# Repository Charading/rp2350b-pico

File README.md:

# RP2350B Pico Board

This is a custom RP2350B development board designed to match the **Raspberry Pi Pico** form factor.  
It keeps a similar form factor but is extended by a few pins, in order to break out all 8 analog gpio.

---

## Features
- **RP2350B microcontroller**
- **Pico-compatible pinout**
- **USB-C connector**
- **WS2812 RGB LED** on **GPIO16**
- **BOOT** and **RESET** buttons
- **Castellated edges** for module or breadboard use

---

## Notes
- The WS2812 LED on **GPIO16** can be controlled using any standard NeoPixel or WS2812 library.
- The board powers from **USB 5V (VBUS)** through a Schottky diode to **VSYS**,  
  then regulated down to **3.3V** for the MCU.
- Fully compatible with the **Raspberry Pi Pico SDK**, **MicroPython**, and **CircuitPython**.

### Expansion Board
I also created a small expansion board since it doesn't follow the exact layout as the original Pico.

---

Designed for experimentation and easy migration from RP2040 to RP2350 as I wanted more analog pins for a project.
Inspiration taken from  [pico-stretch](https://github.com/jvanderberg/pico-stretch) by [jvanderberg](https://github.com/jvanderberg)

---

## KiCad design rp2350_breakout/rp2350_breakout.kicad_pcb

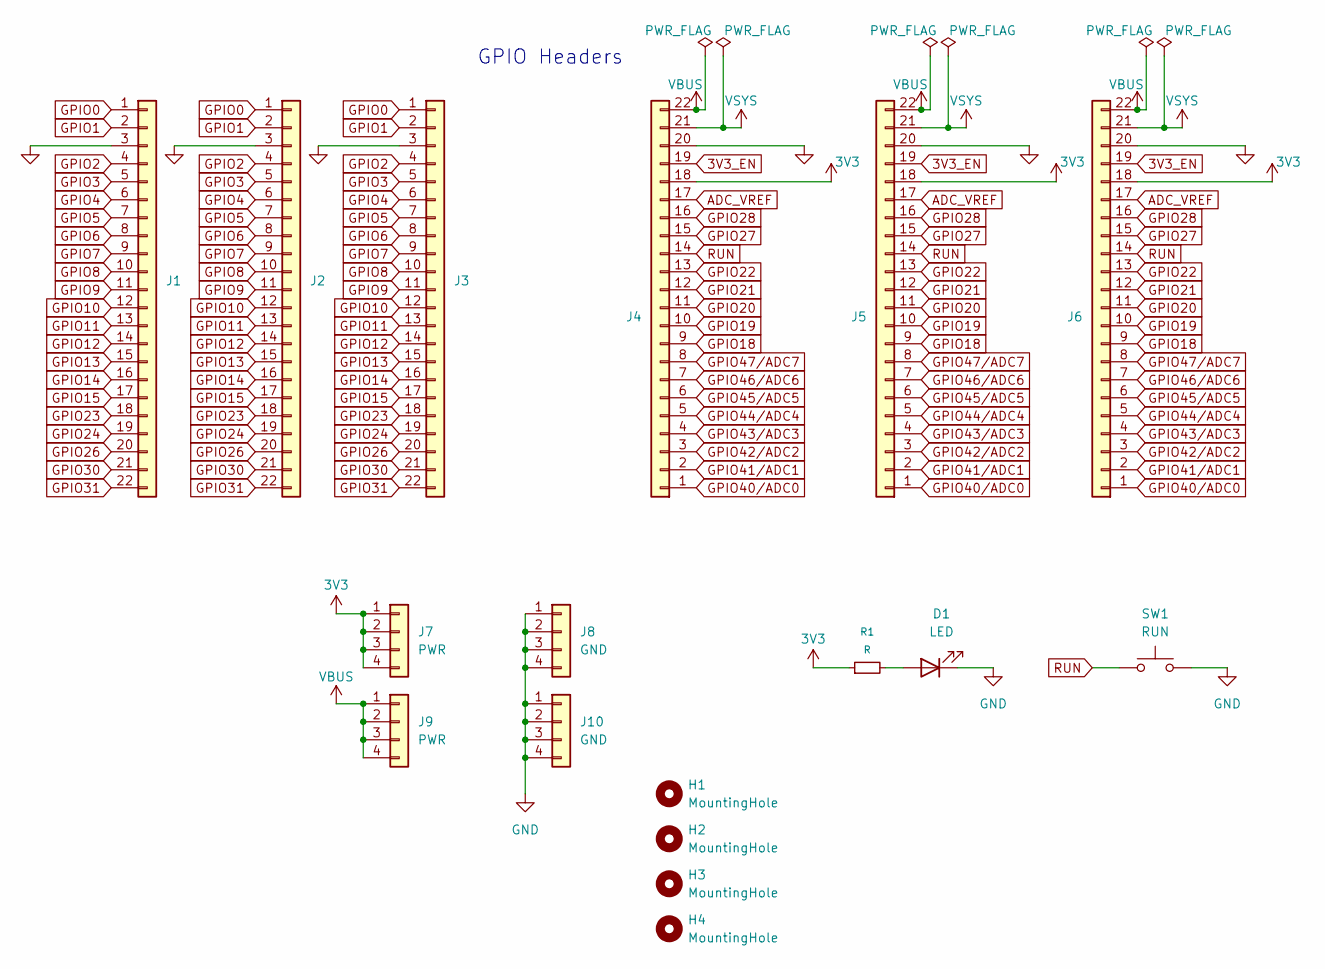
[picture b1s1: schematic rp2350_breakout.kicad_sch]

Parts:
D1: LED; LED_0805_2012Metric
H1, H2, H3, H4: MountingHole; MountingHole_2.2mm_M2
J1, J2, J3, J4, J5, J6: Conn_01x32_MountingPin; Mars_Clean_Connector_01x22_PinHeader_2.54mm
J7, J9: PWR; SWD_Debug_PinHeader_1x04_P2.54mm; Part Number 1-0401FBV0T
J8, J10: GND; SWD_Debug_PinHeader_1x04_P2.54mm; Part Number 1-0401FBV0T
R1: R; R_0805
SW1: RUN; SW_TH_Tactile_Omron_B3F-102x

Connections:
3V3: J4.18, J5.18, J6.18, J7.1, J7.2, J7.3, J7.4, R1.1
3V3_EN: J4.19, J5.19, J6.19
ADC_VREF: J4.17, J5.17, J6.17
GND: D1.1 (K), J1.3, J2.3, J3.3, J4.20, J5.20, J6.20, J8.1, J8.2, J8.3, J8.4, J10.1, J10.2, J10.3, J10.4, SW1.2; also elsewhere on the board
GPIO0: J1.1, J2.1, J3.1
GPIO1: J1.2, J2.2, J3.2
GPIO2: J1.4, J2.4, J3.4
GPIO3: J1.5, J2.5, J3.5
GPIO4: J1.6, J2.6, J3.6
GPIO5: J1.7, J2.7, J3.7
GPIO6: J1.8, J2.8, J3.8
GPIO7: J1.9, J2.9, J3.9
GPIO8: J1.10, J2.10, J3.10
GPIO9: J1.11, J2.11, J3.11
GPIO10: J1.12, J2.12, J3.12
GPIO11: J1.13, J2.13, J3.13
GPIO12: J1.14, J2.14, J3.14
GPIO13: J1.15, J2.15, J3.15
GPIO14: J1.16, J2.16, J3.16
GPIO15: J1.17, J2.17, J3.17
GPIO18: J4.9, J5.9, J6.9
GPIO19: J4.10, J5.10, J6.10
GPIO20: J4.11, J5.11, J6.11
GPIO21: J4.12, J5.12, J6.12
GPIO22: J4.13, J5.13, J6.13
GPIO23: J1.18, J2.18, J3.18
GPIO24: J1.19, J2.19, J3.19
GPIO26: J1.20, J2.20, J3.20
GPIO27: J4.15, J5.15, J6.15
GPIO28: J4.16, J5.16, J6.16
GPIO30: J1.21 (Pin_19), J2.21 (Pin_19), J3.21 (Pin_19)
GPIO31: J1.22 (Pin_20), J2.22 (Pin_20), J3.22 (Pin_20)
GPIO40/ADC0: J4.1, J5.1, J6.1
GPIO41/ADC1: J4.2, J5.2, J6.2
GPIO42/ADC2: J4.3, J5.3, J6.3
GPIO43/ADC3: J4.4, J5.4, J6.4
GPIO44/ADC4: J4.5, J5.5, J6.5
GPIO45/ADC5: J4.6, J5.6, J6.6
GPIO46/ADC6: J4.7, J5.7, J6.7
GPIO47/ADC7: J4.8, J5.8, J6.8
unnamed 40: D1.2 (A), R1.2; also elsewhere on the board
RUN: J4.14, J5.14, J6.14, SW1.1
VBUS: J4.22 (Pin_20), J5.22 (Pin_20), J6.22 (Pin_20), J9.1, J9.2, J9.3, J9.4
VSYS: J4.21 (Pin_19), J5.21 (Pin_19), J6.21 (Pin_19)

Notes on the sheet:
GPIO Headers

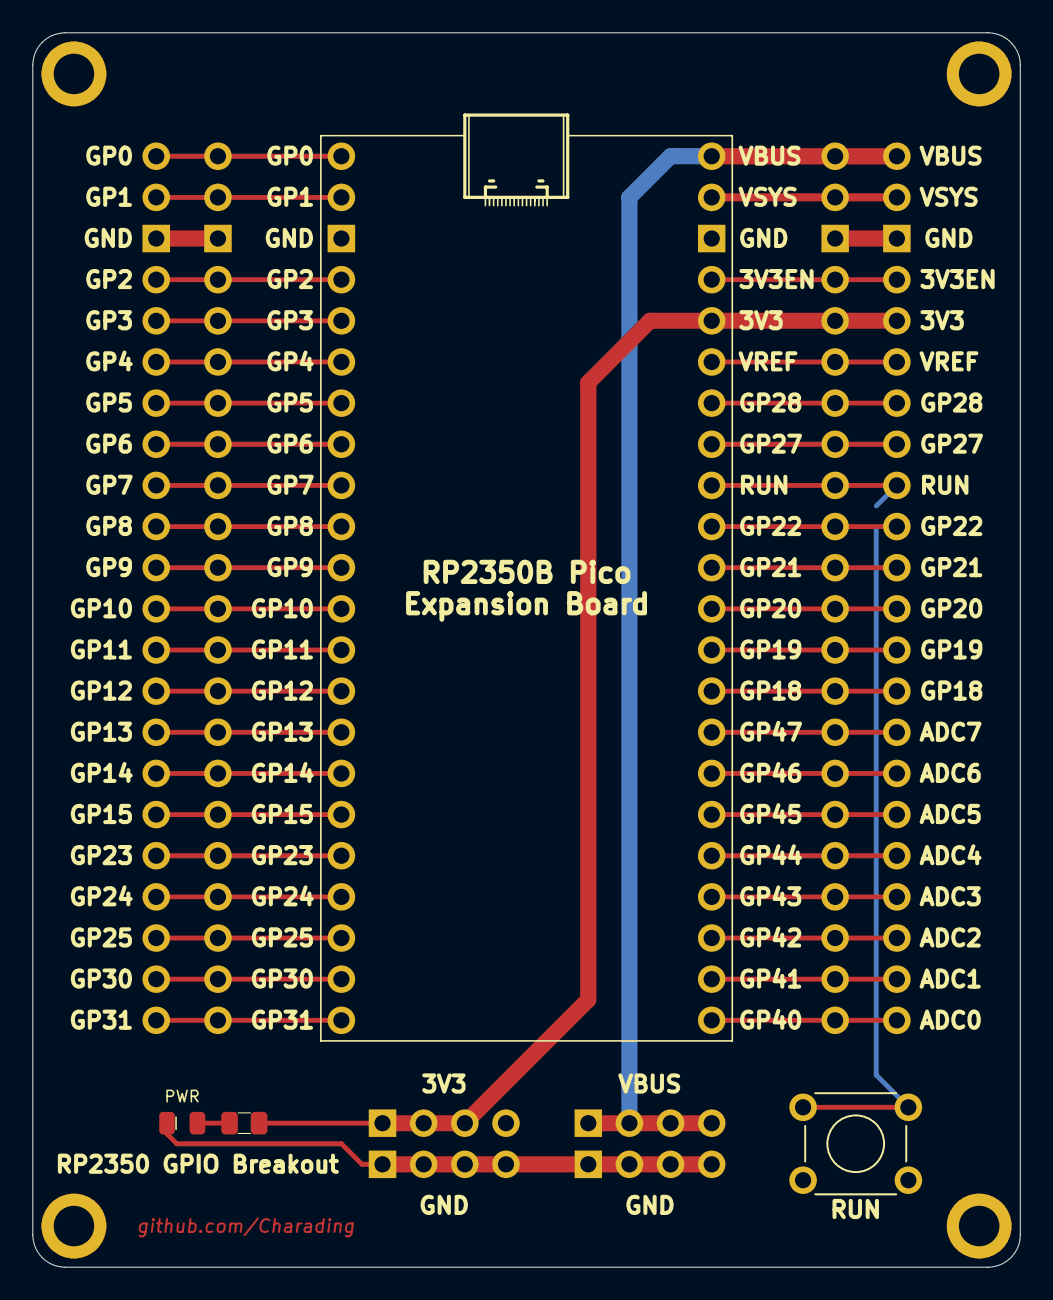
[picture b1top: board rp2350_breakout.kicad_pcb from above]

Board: 2 copper layers, 61.0 x 76.2 mm, 17 parts (0 on the bottom side), 44 nets.

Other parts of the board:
PWR: LED; LED_0805_2012Metric

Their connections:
GND: PWR.1 (K); also elsewhere on the board
unnamed 40: PWR.2 (A); also elsewhere on the board

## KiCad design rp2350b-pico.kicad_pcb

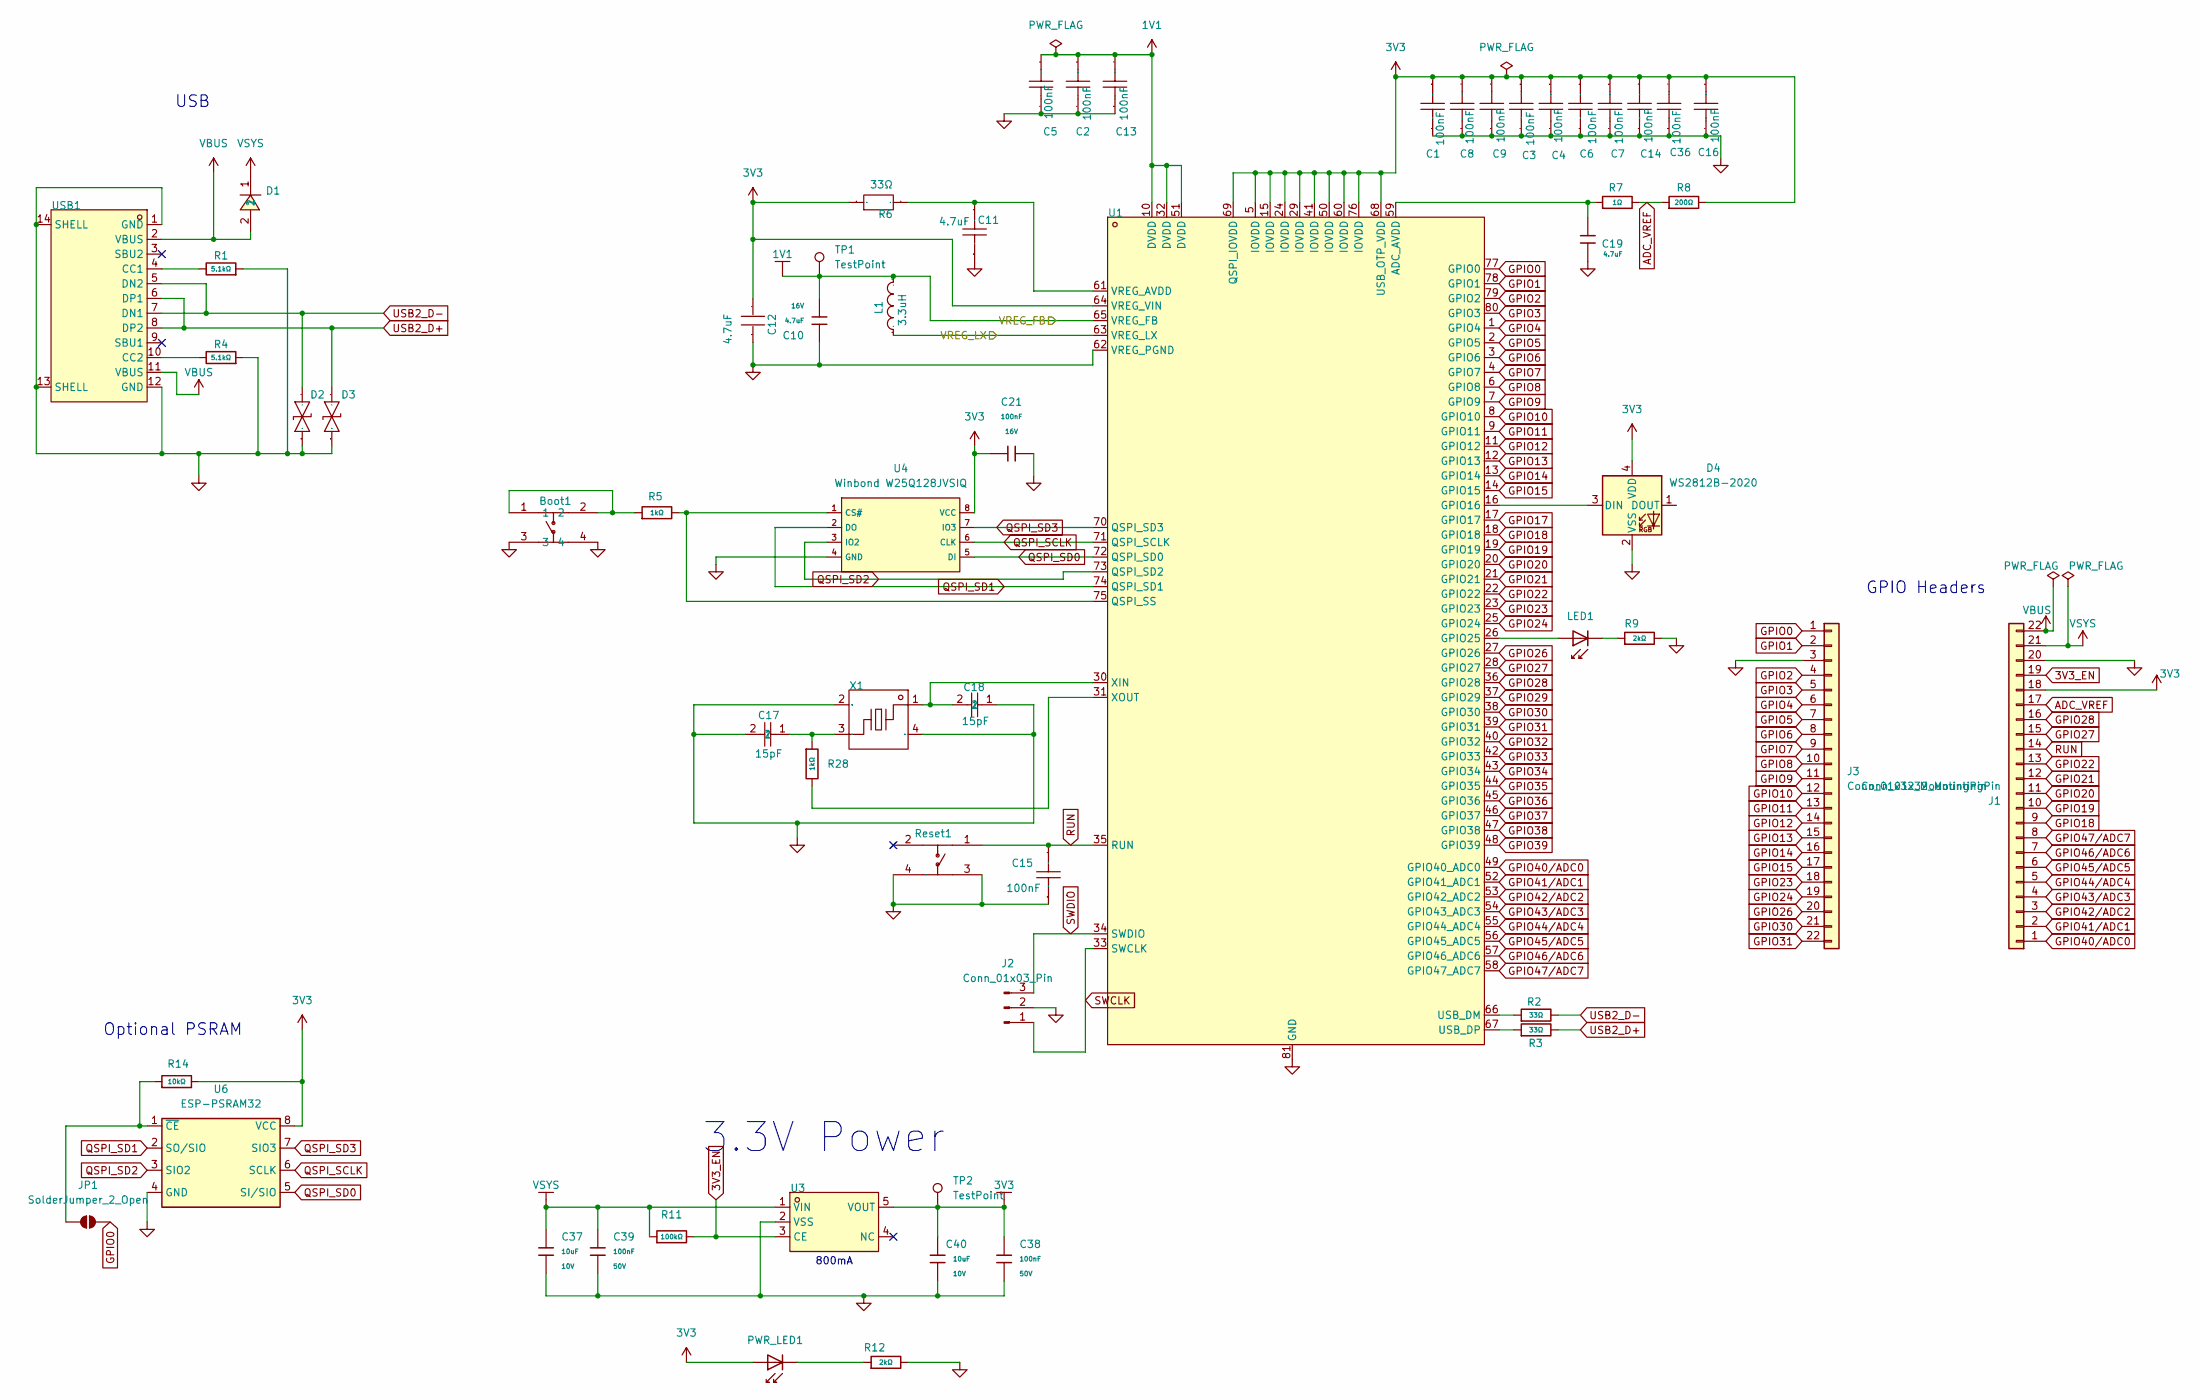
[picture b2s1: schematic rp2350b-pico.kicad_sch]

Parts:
Boot1: K2-1808SN-A4SW-01; KEY-SMD_4P-L4.2-W3.2-P2.20-LS5.1-TL; Manufacturer Part K2-1808SN-A4SW-01; LCSC Part Name 4.2mm*3.25mm
C1, C2, C3, C4, C5, C6, C7, C8, C13, C14, C16, C36: 100nF; C0402; Manufacturer Part CL05B104KO5NNNC; LCSC Part Name 100nF ±10% 16V
C9, C15: 100nF; C0402; Voltage Rating 50V; Manufacturer Part CC0603KRX7R9BB104; LCSC Part Name 100nF ±10% 50V
C10: 4.7uF; C_0603; Voltage Rated 16V; Tolerance ±10%; Part CL10A475KO8NNNC; LCSC C19666
C11: 4.7uF; Manufacturer Part CL05A475MP5NRNC; LCSC Part Name 4.7uF ±20% 10V
C12: 4.7uF; Manufacturer Part CL10A475KO8NNNC; LCSC Part Name 4.7uF ±10% 16V
C17, C18: 15pF; C0402; Manufacturer Part 0402CG150J500NT; LCSC Part Name 15pF ±5% 50V
C19: 4.7uF; C_0402; Voltage Rated 10V; Tolerance ±20%; Part CL05A475MP5NRNC; LCSC C23733
C21: 100nF; C_0402; Voltage Rated 16V; Tolerance ±10%; Part CL05B104KO5NNNC; LCSC C1525
C37, C40: 10uF; C_0603; Voltage Rated 10V; Tolerance ±10%; Part CL10A106KP8NNNC; LCSC C19702
C38, C39: 100nF; C_0603; Voltage Rated 50V; Tolerance ±10%; Part CC0603KRX7R9BB104; LCSC C14663
D1: POWERDI-123_L2.8-W1.8-LS3.7-RD; Manufacturer Part DFLS130L-7; LCSC Part Name 电压:30V 电流:1A
D2, D3: RCLAMP0521P.TCT-MS; D0402-BI; Manufacturer Part RCLAMP0521P.TCT-MS; LCSC Part Name 双向TVS 5V截止 4A峰值脉冲 丝印N
D4: WS2812B-2020; LED_WS2812B-2020_PLCC4_2.0x2.0mm
J1, J3: Conn_01x32_MountingPin; Pico_22pin
J2: Conn_01x03_Pin; PinHeader_1x03_P2.54mm_Vertical
JP1: SolderJumper_2_Open; JUMPER_SMD_1x2_tiny
L1: IND-SMD_L2.0-W1.6_AOTA-B201610S3R3-101-T; Manufacturer Part AOTA-B201610S3R3-101-T; LCSC Part Name AOTA-B201610S3R3-101-T
LED1: Red; Mars_LED_0603; Part KT-0603R; LCSC C2286
PWR_LED1: Red; D_0603; Part KT-0603R; LCSC C2286
R1, R4: 5.1kΩ; R_0402; Overload Voltage (Max) 50V; Tolerance ±1%; Part 0402WGF5101TCE; LCSC C25905
R2, R3: 33Ω; R_0402; Overload Voltage (Max) 50V; Tolerance ±1%; Part 0402WGF330JTCE; LCSC C25105
R5: 1kΩ; R_0402; Overload Voltage (Max) 50V; Tolerance ±1%; Part 0402WGF1001TCE; LCSC C11702
R6: 33Ω; R0402; Manufacturer Part 0402WGF330JTCE; LCSC Part Name 33Ω ±1% 62.5mW 厚膜电阻
R7: 1Ω; R_0603; Overload Voltage (Max) 75V; Tolerance ±1%; Part 0603WAF100KT5E; LCSC C22936
R8: 200Ω; R_0603; Overload Voltage (Max) 75V; Tolerance ±1%; Part 0603WAF2000T5E; LCSC C8218
R9, R12: 2kΩ; R_0402; Overload Voltage (Max) 50V; Tolerance ±1%; Part 0402WGF2001TCE; LCSC C4109
R11: 100kΩ; R_0402; Overload Voltage (Max) 50V; Tolerance ±1%; Part 0402WGF1003TCE; LCSC C25741
R14: 10kΩ; R_0402; Overload Voltage (Max) 50V; Tolerance ±1%; Part 0402WGF1002TCE; LCSC C25744
R28: 1kΩ; R_0603; Overload Voltage (Max) 75V; Tolerance ±1%; Part 0603WAF1001T5E; LCSC C21190
Reset1: K2-1808SN-A4SW-01; KEY-SMD_4P-L4.2-W3.2-P2.20-LS5.1-TL; Manufacturer Part K2-1808SN-A4SW-01; LCSC Part Name 4.2mm*3.25mm
TP1, TP2: TestPoint; TestPoint_Pad_1.0x1.0mm
U1: QFN-80_L10.0-W10.0-P0.40-TL-EP3.4; Manufacturer Part RP2350B; LCSC Part Name RP2350B
U3: SOT-23-5_L3.0-W1.7-P0.95-LS2.8-BR; Manufacturer Part ME6217C33M5G; LCSC Part Name ME6217C33M5G
U4: Winbond W25Q128JVSIQ; SOIC-8_L5.3-W5.3-P1.27-LS8.0-BL; Part W25Q128JVSIQ; LCSC C97521
U6: ESP-PSRAM32; SOIC-8_3.9x4.9mm_P1.27mm
USB1: USB-C-SMD_TYPE-C-6PIN-2MD-073; Manufacturer Part TYPE-C 16PIN 2MD(073); LCSC Part Name Type-C 母 卧贴
X1: Manufacturer Part ABM8-272-T3; LCSC Part Name ABM8-272-T3

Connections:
1V1: C2.1, C5.1, C10.2, C13.2, L1.2, TP1.1, U1.10 (DVDD), U1.32 (DVDD), U1.51 (DVDD), U1.65 (VREG_FB)
3V3: C1.1, C3.1, C4.1, C6.1, C7.1, C8.2, C9.2, C12.2, C14.2, C16.1, C21.1, C36.2, C38.1, C40.1, D4.4 (VDD), J1.18, PWR_LED1.2, R6.1, R8.2, R14.2, TP2.1, U1.5 (IOVDD), U1.15 (IOVDD), U1.24 (IOVDD), U1.29 (IOVDD), U1.41 (IOVDD), U1.50 (IOVDD), U1.60 (IOVDD), U1.64 (VREG_VIN), U1.68 (USB_OTP_VDD), U1.69 (QSPI_IOVDD), U1.76 (IOVDD), U3.5 (VOUT), U4.8 (VCC), U6.8 (VCC); also elsewhere on the board
3V3_EN: J1.19, R11.2, U3.3 (CE)
/VREG_LX: L1.1, U1.63 (VREG_LX)
ADC_VREF: J1.17, R7.2, R8.1
GND: Boot1.3, Boot1.4, C1.2, C2.2, C3.2, C4.2, C5.2, C6.2, C7.2, C8.1, C9.1, C10.1, C11.1, C12.1, C13.1, C14.1, C15.1, C16.2, C17.2, C18.1, C19.2, C21.2, C36.1, C37.2, C38.2, C39.2, C40.2, D2.1, D3.1, D4.2 (VSS), J1.20, J2.2, J3.3, R1.1, R4.1, R9.2, R12.2, Reset1.3, Reset1.4, U1.62 (VREG_PGND), U1.81 (GND), U3.2 (VSS), U4.4 (GND), U6.4 (GND), USB1.1 (GND), USB1.12 (GND), USB1.13 (SHELL), USB1.14 (SHELL), X1.2 (GND), X1.4 (GND); also elsewhere on the board
GPIO0: J3.1, JP1.2 (B), U1.77 (GPIO0)
GPIO1: J3.2, U1.78 (GPIO1)
GPIO2: J3.4, U1.79 (GPIO2)
GPIO3: J3.5, U1.80 (GPIO3)
GPIO4: J3.6, U1.1 (GPIO4)
GPIO5: J3.7, U1.2 (GPIO5)
GPIO6: J3.8, U1.3 (GPIO6)
GPIO7: J3.9, U1.4 (GPIO7)
GPIO8: J3.10, U1.6 (GPIO8)
GPIO9: J3.11, U1.7 (GPIO9)
GPIO10: J3.12, U1.8 (GPIO10)
GPIO11: J3.13, U1.9 (GPIO11)
GPIO12: J3.14, U1.11 (GPIO12)
GPIO13: J3.15, U1.12 (GPIO13)
GPIO14: J3.16, U1.13 (GPIO14)
GPIO15: J3.17, U1.14 (GPIO15)
GPIO17: U1.17 (GPIO17)
GPIO18: J1.9, U1.18 (GPIO18)
GPIO19: J1.10, U1.19 (GPIO19)
GPIO20: J1.11, U1.20 (GPIO20)
GPIO21: J1.12, U1.21 (GPIO21)
GPIO22: J1.13, U1.22 (GPIO22)
GPIO23: J3.18, U1.23 (GPIO23)
GPIO24: J3.19, U1.25 (GPIO24)
GPIO26: J3.20, U1.27 (GPIO26)
GPIO27: J1.15, U1.28 (GPIO27)
GPIO28: J1.16, U1.36 (GPIO28)
GPIO29: U1.37 (GPIO29)
GPIO30: J3.21 (Pin_19), U1.38 (GPIO30)
GPIO31: J3.22 (Pin_20), U1.39 (GPIO31)
GPIO32: U1.40 (GPIO32)
GPIO33: U1.42 (GPIO33)
GPIO34: U1.43 (GPIO34)
GPIO35: U1.44 (GPIO35)
GPIO36: U1.45 (GPIO36)
GPIO37: U1.46 (GPIO37)
GPIO38: U1.47 (GPIO38)
GPIO39: U1.48 (GPIO39)
GPIO40/ADC0: J1.1, U1.49 (GPIO40_ADC0)
GPIO41/ADC1: J1.2, U1.52 (GPIO41_ADC1)
GPIO42/ADC2: J1.3, U1.53 (GPIO42_ADC2)
GPIO43/ADC3: J1.4, U1.54 (GPIO43_ADC3)
GPIO44/ADC4: J1.5, U1.55 (GPIO44_ADC4)
GPIO45/ADC5: J1.6, U1.56 (GPIO45_ADC5)
GPIO46/ADC6: J1.7, U1.57 (GPIO46_ADC6)
GPIO47/ADC7: J1.8, U1.58 (GPIO47_ADC7)
unnamed: Boot1.1, Boot1.2, R5.1
unnamed: C17.1, R28.1, X1.3
unnamed: D4.3 (DIN), U1.16 (GPIO16)
unnamed: JP1.1 (A), R14.1, U6.1 (~CE)
unnamed: LED1.1, R9.1
unnamed: PWR_LED1.1, R12.1
unnamed: C19.1, R7.1, U1.59 (ADC_AVDD)
unnamed: LED1.2, U1.26 (GPIO25)
unnamed: R5.2, U1.75 (QSPI_SS), U4.1 (CS#)
unnamed: R2.1, U1.66 (USB_DM)
unnamed: R3.1, U1.67 (USB_DP)
unnamed: C11.2, R6.2, U1.61 (VREG_AVDD)
unnamed: C18.2, U1.30 (XIN), X1.1
unnamed: R28.2, U1.31 (XOUT)
unnamed: R1.2, USB1.4 (CC1)
unnamed: R4.2, USB1.10 (CC2)
QSPI_SCLK: U1.71 (QSPI_SCLK), U4.6 (CLK), U6.6 (SCLK)
QSPI_SD0: U1.72 (QSPI_SD0), U4.5 (DI), U6.5 (SI/SIO)
QSPI_SD1: U1.74 (QSPI_SD1), U4.2 (DO), U6.2 (SO/SIO)
QSPI_SD2: U1.73 (QSPI_SD2), U4.3 (IO2), U6.3 (SIO2)
QSPI_SD3: U1.70 (QSPI_SD3), U4.7 (IO3), U6.7 (SIO3)
RUN: C15.2, J1.14, Reset1.1, U1.35 (RUN)
SWCLK: J2.1, U1.33 (SWCLK)
SWDIO: J2.3, U1.34 (SWDIO)
USB2_D+: D3.2, R3.2, USB1.6 (DP1), USB1.8 (DP2)
USB2_D-: D2.2, R2.2, USB1.5 (DN2), USB1.7 (DN1)
VBUS: D1.2, J1.22 (Pin_20), USB1.2 (VBUS), USB1.11 (VBUS)
VSYS: C37.1, C39.1, D1.1, J1.21 (Pin_19), R11.1, U3.1 (VIN)

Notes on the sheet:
Optional PSRAM
3.3V Power
GPIO Headers
USB
800mA

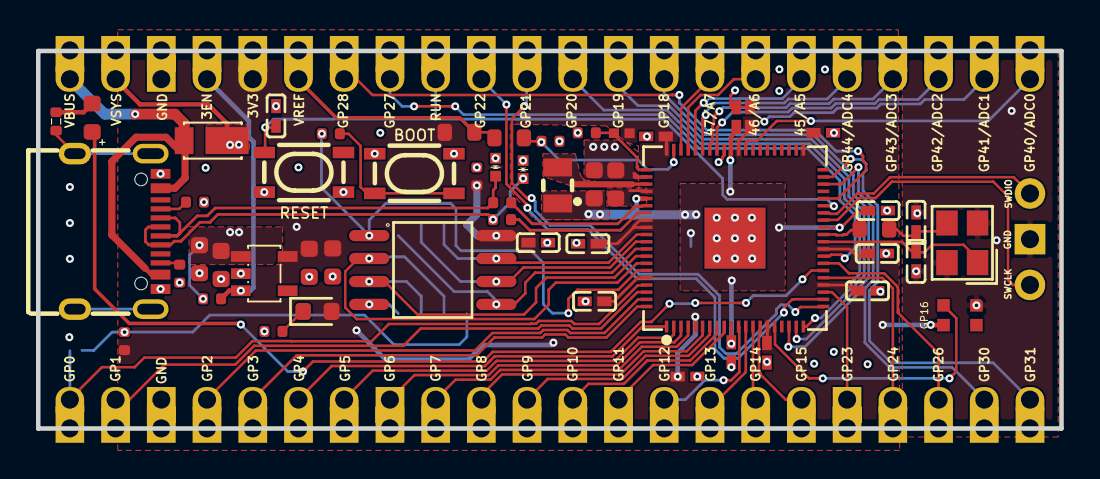
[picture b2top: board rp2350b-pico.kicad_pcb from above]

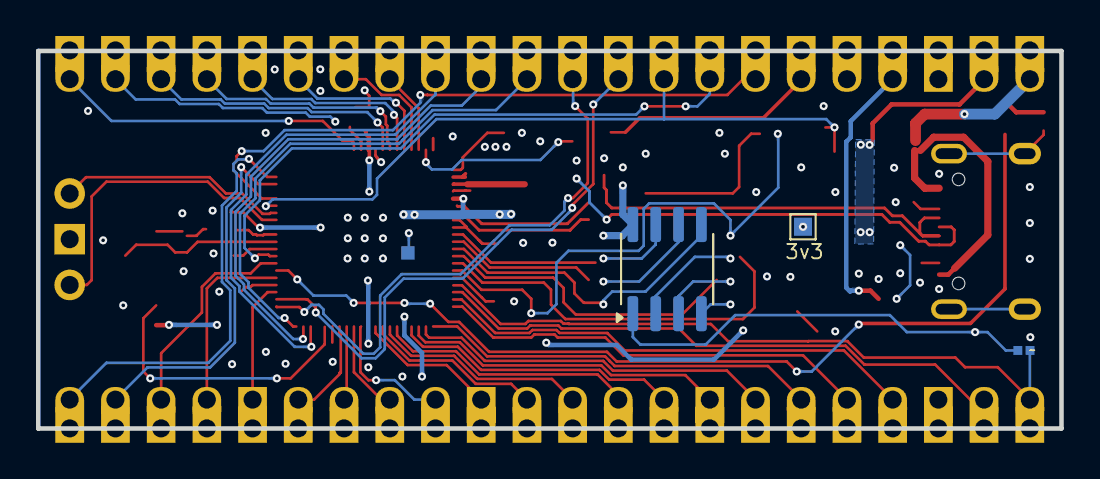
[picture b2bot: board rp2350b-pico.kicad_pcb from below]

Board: 4 copper layers, 56.8 x 21.0 mm, 59 parts (4 on the bottom side), 70 nets.

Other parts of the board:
C22: 100nF; C_0402

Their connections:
3V3: C22.1; also elsewhere on the board
GND: C22.2; also elsewhere on the board

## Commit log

2025-11-05 Revise README to enhance board description
    Updated the description to clarify the board's features and inspiration.
2025-11-06 designed gpio expansion board
2025-11-13 updated readme to include expansion board
